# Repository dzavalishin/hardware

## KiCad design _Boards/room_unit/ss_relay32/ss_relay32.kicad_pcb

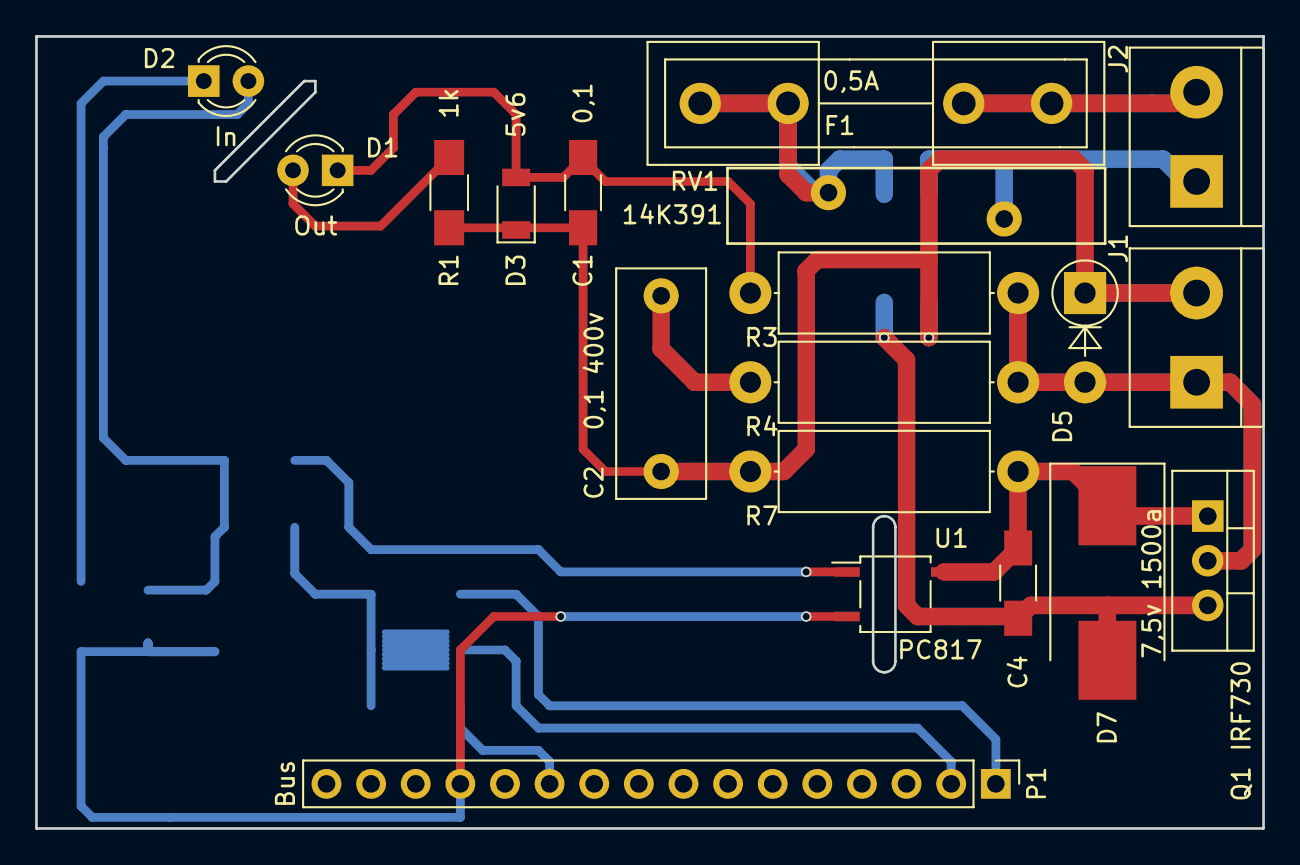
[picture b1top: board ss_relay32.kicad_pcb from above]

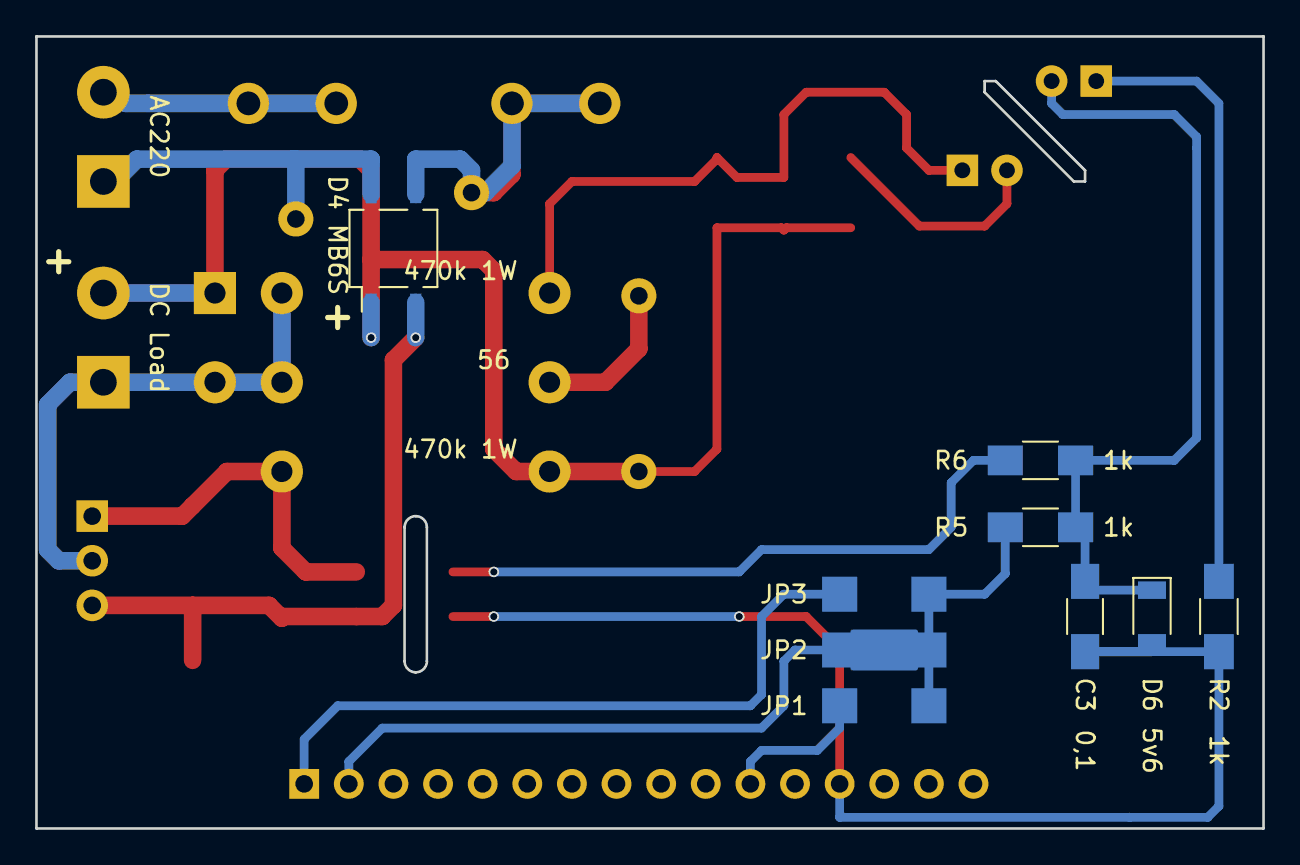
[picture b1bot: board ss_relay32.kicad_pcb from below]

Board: 2 copper layers, 69.8 x 45.1 mm, 28 parts (9 on the bottom side), 18 nets.

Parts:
C1, C3, C4: 0,1; C_1206_HandSoldering
C2: 0,1 400v; C_Rect_L13.0mm_W5.0mm_P10.00mm_FKS3_FKP3_MKS4
D1: Out; LED_D3.0mm
D2: In; LED_D3.0mm
D3, D6: 5v6; D_1206
D4: MB6S; Diode_Bridge_TO-269AA
D5: RL206; D_DO-15_P5.08mm_Vertical_AnodeUp
D7: 7,5v 1500a; D_SMC_Handsoldering
F1: 0,5A; Fuseholder5x20_horiz_open_inline_Type-I
J1: DC Load; TerminalBlock_bornier-2_P5.08mm
J2: AC220; TerminalBlock_bornier-2_P5.08mm
JP1, JP3: Jumper; NetTie-I_SMD
JP2: Jumper; NetTie-I_Connected_SMD
P1: Bus; Pin_Header_Straight_1x16_Pitch2.54mm
Q1: IRF730; TO-220-3_Vertical
R1, R2, R5, R6: 1k; R_1206_HandSoldering
R3, R7: 470k 1W; R_Axial_DIN0414_L11.9mm_D4.5mm_P15.24mm_Horizontal
R4: 56; R_Axial_DIN0414_L11.9mm_D4.5mm_P15.24mm_Horizontal
RV1: 14K391; RV_Disc_D21.5_W4.3_P10
U1: PC817; SOP-4_3.8x4.1mm_Pitch2.54mm

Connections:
/+220: C1.1, C2.1, D3.1, D4.1, D5.1, J1.2, R1.1, R7.1
/DO0: JP2.1, P1.2
/DO1: JP3.1, P1.1
/DO2: JP1.1, P1.11
/Gate: C4.1, D7.1, Q1.1, R7.2, U1.4
/IN: JP1.2, JP2.2, JP3.2, R5.2
/Load: D5.2, J1.1, Q1.2, R3.2, R4.2
/OGND: C4.2, D4.2, D7.2, Q1.3, U1.3
GND: C3.2, D6.2, P1.13, R2.2, U1.2
unnamed: C1.2, D1.1, D3.2, R3.1
unnamed: C2.2, R4.1
unnamed: C3.1, D2.2, D6.1, R5.1, R6.2
unnamed: D1.2, R1.2
unnamed: D2.1, R2.1
unnamed: D4.3, F1.2, RV1.1
unnamed: D4.4, J2.1, RV1.2
unnamed: F1.1, J2.2
unnamed: R6.1, U1.1

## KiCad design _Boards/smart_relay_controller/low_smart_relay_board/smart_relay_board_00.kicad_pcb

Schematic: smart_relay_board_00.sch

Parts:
C1, C32, C33: 0,1; C_1206_HandSoldering
C34: 47,0; CP_Elec_6.3x7.7
D23: 1n4148; D_MiniMELF_Handsoldering
J1: Di0-2; TerminalBlock_bornier-4_P5.08mm
J2: Di3-5; TerminalBlock_bornier-4_P5.08mm
J3: Di_6; TerminalBlock_bornier-2_P5.08mm
J4: Di_7; TerminalBlock_bornier-2_P5.08mm
J13: CPU; Pin_Header_Straight_2x06_Pitch2.54mm
J14: Power; TerminalBlock_bornier-2_P5.08mm
J15: RS485; TerminalBlock_bornier-2_P5.08mm
J16: Term485; Pin_Header_Straight_1x02_Pitch2.54mm
Q1: Q_NMOS_DGS; TO-92_Molded_Narrow_Oval
R4, R25: 1k; R_1206_HandSoldering
R20: 47; R_1206_HandSoldering
R24: 47k; R_1206_HandSoldering
U3: TPIC6595; DIP-20_W7.62mm_Socket_LongPads
U4: 74LS166; DIP-16_W7.62mm_Socket_LongPads

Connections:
+5V: C32.1, C33.1, C34.1, J13.7, R4.1, R24.1, U3.2, U4.16 (VCC); also elsewhere on the board
/MISO: D23.2, J13.2
/MOSI: J13.1, U3.3
/SCK: J13.5, U3.13, U4.7 (Clk)
/SS1: J13.4, Q1.3, U4.15 (PE)
/Sheet_relay_pair_0/Relay_In_Minus: J1.2; also elsewhere on the board
/Sheet_relay_pair_0/Relay_In_Plus: J1.1; also elsewhere on the board
/Sheet_relay_pair_1/Relay_In_Minus: J1.3; also elsewhere on the board
/Sheet_relay_pair_2/Relay_In_Minus: J1.4; also elsewhere on the board
/Sheet_relay_pair_4/Relay_In_Minus: J2.3; also elsewhere on the board
/Sheet_relay_pair_5/Relay_In_Minus: J2.4; also elsewhere on the board
/Simple_Di_Do_6/DI_B: J3.2; also elsewhere on the board
/Simple_Di_Do_6/Di_A: J3.1; also elsewhere on the board
/Simple_Di_Do_7/DI_B: J4.2; also elsewhere on the board
/Simple_Di_Do_7/Di_A: J4.1; also elsewhere on the board
/~CLR: C1.1, R4.2, U3.8, U4.9 (Clr)
/~SS0: J13.3, U3.12
CPU_Di0: U4.2 (A); also elsewhere on the board
CPU_Di1: U4.3 (B); also elsewhere on the board
CPU_Di2: U4.4 (C); also elsewhere on the board
CPU_Di3: U4.5 (D); also elsewhere on the board
CPU_Di4: U4.10 (E); also elsewhere on the board
CPU_Di5: U4.11 (F); also elsewhere on the board
CPU_Di6: U4.12 (G); also elsewhere on the board
CPU_Di7: U4.14 (H); also elsewhere on the board
CPU_Do0: U3.4; also elsewhere on the board
CPU_Do1: U3.5; also elsewhere on the board
CPU_Do2: U3.6; also elsewhere on the board
CPU_Do3: U3.7, U3.14; also elsewhere on the board
CPU_Do5: U3.15; also elsewhere on the board
CPU_Do6: U3.16; also elsewhere on the board
CPU_Do7: U3.17; also elsewhere on the board
GND: C1.2, C32.2, C33.2, C34.2, J13.6, J13.8, U3.1, U3.9, U3.10, U3.11, U3.19, U3.20, U4.1 (Ds), U4.6 (CE), U4.8 (GND); also elsewhere on the board
unnamed: D23.1, Q1.1, R24.2
unnamed: J13.9, J14.1
unnamed: J13.10, J15.2, R20.2
unnamed: J13.11, J14.2
unnamed: J13.12, J15.1, J16.1
unnamed: J16.2, R20.1
unnamed: Q1.2, R25.2
unnamed: R25.1, U4.13 (Qh)

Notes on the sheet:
Poor man's 3 state out

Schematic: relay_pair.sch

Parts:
C2, C4, C7: 0,1; C_1206_HandSoldering
C3: 0,022 x 400v; C_Rect_L13.0mm_W5.0mm_P10.00mm_FKS3_FKP3_MKS4
D1: 5v6; D_MiniMELF_Handsoldering
D3: 1n4148; D_MiniMELF_Handsoldering
D5: MB6S; SO-4_4.4x3.6mm_Pitch2.54mm
J5: Do_Adv; TerminalBlock_bornier-3_P5.08mm
R1, R2, R5: 1k; R_1206_HandSoldering
R3: 100 1w; R_Axial_DIN0309_L9.0mm_D3.2mm_P12.70mm_Horizontal
RL11, RL12: HK4100F; Relay_SPDT_HK4100F
U5: LTV-817; SO-4_7.6x3.6mm_Pitch2.54mm

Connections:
+5V: D3.1, R5.1, RL12.5; also elsewhere on the board
/Sheet_relay_pair_0/Relay_In_Plus: D5.3; also elsewhere on the board
/Sheet_relay_pair_1/Relay_In_Minus: D5.4; also elsewhere on the board
CPU_Di0: C7.1, R5.2, U5.4; also elsewhere on the board
CPU_Do0: D3.2; also elsewhere on the board
CPU_Do3: RL12.2; also elsewhere on the board
GND: C7.2, U5.3; also elsewhere on the board
unnamed 33: C2.1, C4.2, D1.2, U5.2; also elsewhere on the board
unnamed 34: C2.2, D1.1, R1.2, R2.1; also elsewhere on the board
unnamed 35: C3.1, J5.3; also elsewhere on the board
unnamed: C3.2, R3.1
unnamed: C4.1, R2.2, U5.1
unnamed 45: D5.2 (-); also elsewhere on the board
unnamed 56: RL11.5; also elsewhere on the board
unnamed 57: RL11.2; also elsewhere on the board
unnamed 58: RL11.1, RL11.6; also elsewhere on the board
unnamed 71: R1.1; also elsewhere on the board
unnamed 72: D5.1 (+); also elsewhere on the board
unnamed 80: J5.1, R3.2; also elsewhere on the board
unnamed 81: J5.2; also elsewhere on the board
unnamed 90: RL12.1, RL12.6; also elsewhere on the board
unnamed 91: RL11.3, RL12.4; also elsewhere on the board
unnamed: RL11.4, RL12.3

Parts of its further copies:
C5, C8, C10, C11, C13, C14, C16, C17, C25, C26, C27, C28, C29, C30, C31: 0,1; C_1206_HandSoldering
C6, C9, C12, C15, C18: 0,022 x 400v; C_Rect_L13.0mm_W5.0mm_P10.00mm_FKS3_FKP3_MKS4
D2, D8, D11, D14, D17: MB6S; SO-4_4.4x3.6mm_Pitch2.54mm
D4, D7, D10, D13, D16: 5v6; D_MiniMELF_Handsoldering
D6, D9, D12, D15, D18: 1n4148; D_MiniMELF_Handsoldering
J6, J7, J8, J9, J10: Do_Adv; TerminalBlock_bornier-3_P5.08mm
R6, R7, R9, R10, R11, R12, R14, R15, R16, R17, R19, R21, R22, R26, R27: 1k; R_1206_HandSoldering
R8, R13, R18, R23, R28: 100 1w; R_Axial_DIN0309_L9.0mm_D3.2mm_P12.70mm_Horizontal
RL1, RL2, RL3, RL4, RL5, RL6, RL7, RL8, RL9, RL10: HK4100F; Relay_SPDT_HK4100F
U6, U7, U8, U9, U10: LTV-817; SO-4_7.6x3.6mm_Pitch2.54mm

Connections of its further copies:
+5V: D6.1, D9.1, D12.1, D15.1, D18.1, R9.1, R10.1, R14.1, R15.1, R19.1, RL2.5, RL4.5, RL6.5, RL8.5, RL10.5; also elsewhere on the board
/Sheet_relay_pair_0/Relay_In_Minus: D2.4; also elsewhere on the board
/Sheet_relay_pair_0/Relay_In_Plus: D2.3, D8.3; also elsewhere on the board
/Sheet_relay_pair_2/Relay_In_Minus: D8.4; also elsewhere on the board
/Sheet_relay_pair_4/Relay_In_Minus: D17.4; also elsewhere on the board
/Sheet_relay_pair_5/Relay_In_Minus: D11.4; also elsewhere on the board
CPU_Di1: C13.1, R9.2, U6.4; also elsewhere on the board
CPU_Di2: C25.1, R10.2, U7.4; also elsewhere on the board
CPU_Di3: C29.1, R15.2, U9.4; also elsewhere on the board
CPU_Di4: C31.1, R19.2, U10.4; also elsewhere on the board
CPU_Di5: C27.1, R14.2, U8.4; also elsewhere on the board
CPU_Do0: RL2.2; also elsewhere on the board
CPU_Do1: D6.2, RL4.2; also elsewhere on the board
CPU_Do2: D9.2, RL6.2; also elsewhere on the board
CPU_Do3: D15.2, D18.2, RL10.2; also elsewhere on the board
CPU_Do5: D12.2, RL8.2; also elsewhere on the board
GND: C13.2, C25.2, C27.2, C29.2, C31.2, U6.3, U7.3, U8.3, U9.3, U10.3; also elsewhere on the board
unnamed 33: D2.2 (-), RL1.5; also elsewhere on the board
unnamed 34: RL1.2; also elsewhere on the board
unnamed 35: RL1.1, RL1.6; also elsewhere on the board
unnamed: C5.2, D4.1, R6.2, R7.1, RL3.2
unnamed: C6.1, J6.3, RL3.1, RL3.6
unnamed: C6.2, R8.1
unnamed: C8.2, D7.1, R11.2, R12.1, RL5.2
unnamed: C9.1, J7.3, RL5.1, RL5.6
unnamed: C9.2, R13.1
unnamed: C10.1, R7.2, U6.1
unnamed 45: C5.1, C10.2, D4.2, RL3.5, U6.2; also elsewhere on the board
unnamed: C11.1, C26.2, D10.2, D11.2 (-), RL7.5, U8.2
unnamed: C11.2, D10.1, R16.2, R17.1, RL7.2
unnamed: C12.1, J8.3, RL7.1, RL7.6
unnamed: C12.2, R18.1
unnamed: C14.1, C28.2, D13.2, D14.2 (-), RL9.5, U9.2
unnamed: C14.2, D13.1, R21.2, R22.1, RL9.2
unnamed: C15.1, J9.3, RL9.1, RL9.6
unnamed: C15.2, R23.1
unnamed: C16.1, R12.2, U7.1
unnamed: C8.1, C16.2, D7.2, D8.2 (-), RL5.5, U7.2
unnamed 56: C17.1, C30.2, D16.2, D17.2 (-), U10.2; also elsewhere on the board
unnamed 57: C17.2, D16.1, R26.2, R27.1; also elsewhere on the board
unnamed 58: C18.1, J10.3; also elsewhere on the board
unnamed: C18.2, R28.1
unnamed: C26.1, R17.2, U8.1
unnamed: C28.1, R22.2, U9.1
unnamed: C30.1, R27.2, U10.1
unnamed 71: D2.1 (+); also elsewhere on the board
unnamed 72: R6.1; also elsewhere on the board
unnamed: D8.1 (+), R11.1
unnamed: D11.1 (+), R16.1
unnamed: D14.1 (+), R21.1
unnamed: D17.1 (+), R26.1
unnamed 80: RL2.1, RL2.6; also elsewhere on the board
unnamed 81: RL1.3, RL2.4; also elsewhere on the board
unnamed: J6.1, R8.2, RL4.1, RL4.6
unnamed: J6.2, RL3.3, RL4.4
unnamed: J7.1, R13.2, RL6.1, RL6.6
unnamed: J7.2, RL5.3, RL6.4
unnamed: J8.1, R18.2, RL8.1, RL8.6
unnamed: J8.2, RL7.3, RL8.4
unnamed: J9.1, R23.2, RL10.1, RL10.6
unnamed: J9.2, RL9.3, RL10.4
unnamed 90: J10.1, R28.2; also elsewhere on the board
unnamed 91: J10.2; also elsewhere on the board
unnamed: RL1.4, RL2.3
unnamed: RL3.4, RL4.3
unnamed: RL5.4, RL6.3
unnamed: RL7.4, RL8.3
unnamed: RL9.4, RL10.3

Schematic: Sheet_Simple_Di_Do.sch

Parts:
C19, C21: 0,1; C_1206_HandSoldering
C20: 0,022 x 400v; C_Rect_L13.0mm_W5.0mm_P10.00mm_FKS3_FKP3_MKS4
D20: 1N4148; D_MiniMELF_Handsoldering
D21: MB6S; SO-4_4.4x3.6mm_Pitch2.54mm
J11: Do; TerminalBlock_bornier-3_P5.08mm
R31: 22k; R_1206_HandSoldering
R32: 100 1w; R_Axial_DIN0309_L9.0mm_D3.2mm_P12.70mm_Horizontal
R34: 1k; R_1206_HandSoldering
RL14: HK4100F; Relay_SPDT_HK4100F
U1: LTV-817; SO-4_7.6x3.6mm_Pitch2.54mm

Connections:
+5V: D20.1, R34.1, RL14.5; also elsewhere on the board
/Simple_Di_Do_6/Di_A: R31.2; also elsewhere on the board
/Simple_Di_Do_7/DI_B: D21.4; also elsewhere on the board
CPU_Di6: C21.1, R34.2, U1.4; also elsewhere on the board
CPU_Do6: D20.2; also elsewhere on the board
CPU_Do7: RL14.2; also elsewhere on the board
GND: C21.2, U1.3; also elsewhere on the board
unnamed 60: C19.1, U1.1; also elsewhere on the board
unnamed 61: C19.2, U1.2; also elsewhere on the board
unnamed: C20.1, R32.2
unnamed 63: C20.2, J11.2; also elsewhere on the board
unnamed 64: D21.1 (+); also elsewhere on the board
unnamed 65: D21.2 (-); also elsewhere on the board
unnamed 67: RL14.1, RL14.6; also elsewhere on the board
unnamed 77: R31.1; also elsewhere on the board
unnamed 78: D21.3; also elsewhere on the board
unnamed 92: J11.1; also elsewhere on the board
unnamed 93: J11.3, R32.1; also elsewhere on the board
unnamed 94: RL14.3; also elsewhere on the board
unnamed 95: RL14.4; also elsewhere on the board

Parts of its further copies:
C22, C24: 0,1; C_1206_HandSoldering
C23: 0,022 x 400v; C_Rect_L13.0mm_W5.0mm_P10.00mm_FKS3_FKP3_MKS4
D19: MB6S; SO-4_4.4x3.6mm_Pitch2.54mm
D22: 1N4148; D_MiniMELF_Handsoldering
J12: Do; TerminalBlock_bornier-3_P5.08mm
R36: 22k; R_1206_HandSoldering
R37: 100 1w; R_Axial_DIN0309_L9.0mm_D3.2mm_P12.70mm_Horizontal
R39: 1k; R_1206_HandSoldering
RL13: HK4100F; Relay_SPDT_HK4100F
U2: LTV-817; SO-4_7.6x3.6mm_Pitch2.54mm

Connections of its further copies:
+5V: D22.1, R39.1, RL13.5; also elsewhere on the board
/Simple_Di_Do_6/DI_B: D19.4; also elsewhere on the board
/Simple_Di_Do_7/Di_A: R36.2; also elsewhere on the board
CPU_Di7: C24.1, R39.2, U2.4; also elsewhere on the board
CPU_Do6: RL13.2; also elsewhere on the board
CPU_Do7: D22.2; also elsewhere on the board
GND: C24.2, U2.3; also elsewhere on the board
unnamed 60: D19.1 (+); also elsewhere on the board
unnamed 61: D19.2 (-); also elsewhere on the board
unnamed 63: RL13.1, RL13.6; also elsewhere on the board
unnamed 64: C22.1, U2.1; also elsewhere on the board
unnamed 65: C22.2, U2.2; also elsewhere on the board
unnamed: C23.1, R37.2
unnamed 67: C23.2, J12.2; also elsewhere on the board
unnamed 77: D19.3; also elsewhere on the board
unnamed 78: R36.1; also elsewhere on the board
unnamed 92: RL13.3; also elsewhere on the board
unnamed 93: RL13.4; also elsewhere on the board
unnamed 94: J12.1; also elsewhere on the board
unnamed 95: J12.3, R37.1; also elsewhere on the board

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
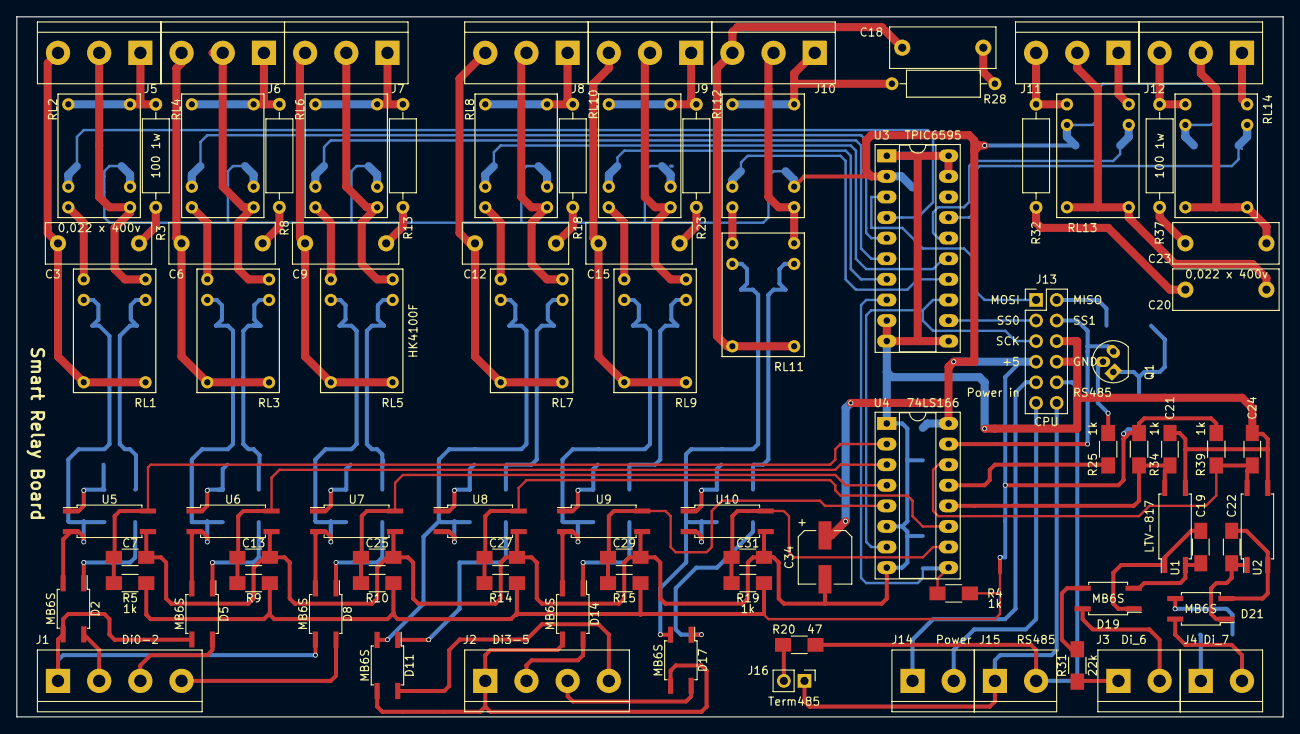
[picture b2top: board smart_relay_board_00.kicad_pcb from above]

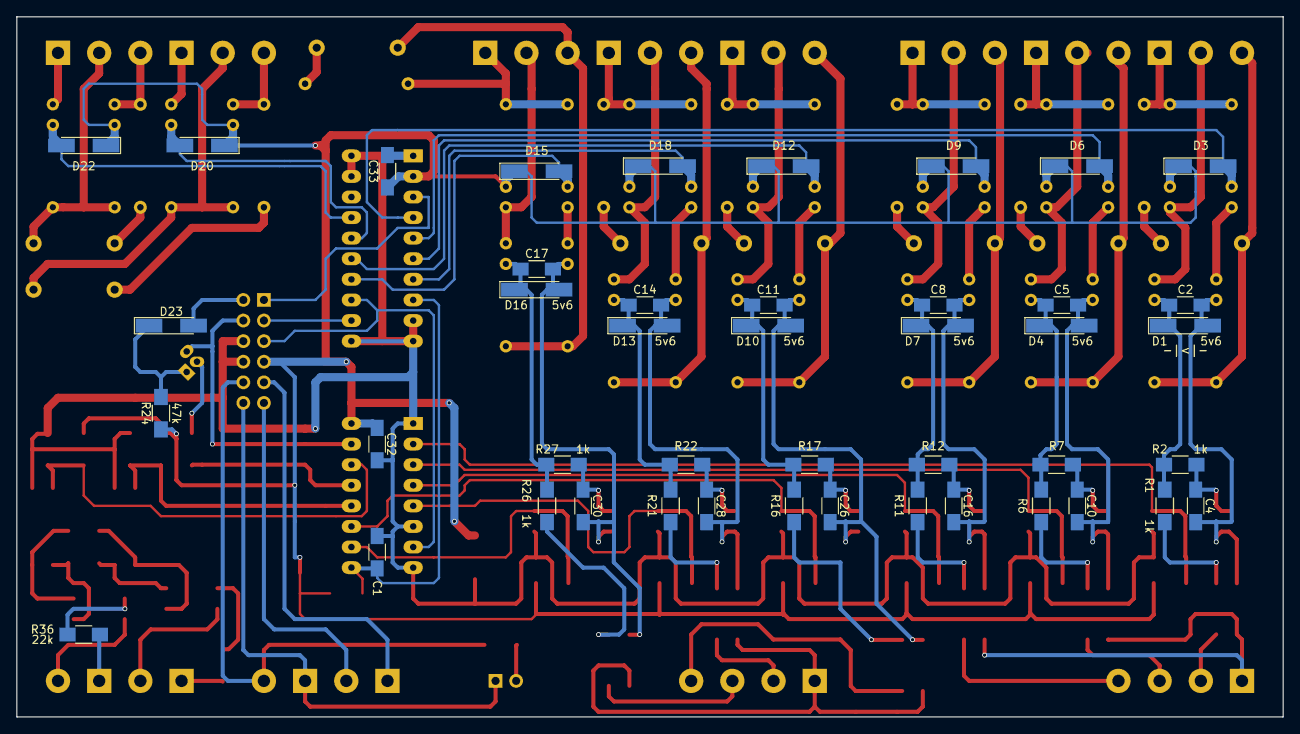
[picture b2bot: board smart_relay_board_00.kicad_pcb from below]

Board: 2 copper layers, 156.2 x 86.4 mm, 132 parts (44 on the bottom side), 111 nets.

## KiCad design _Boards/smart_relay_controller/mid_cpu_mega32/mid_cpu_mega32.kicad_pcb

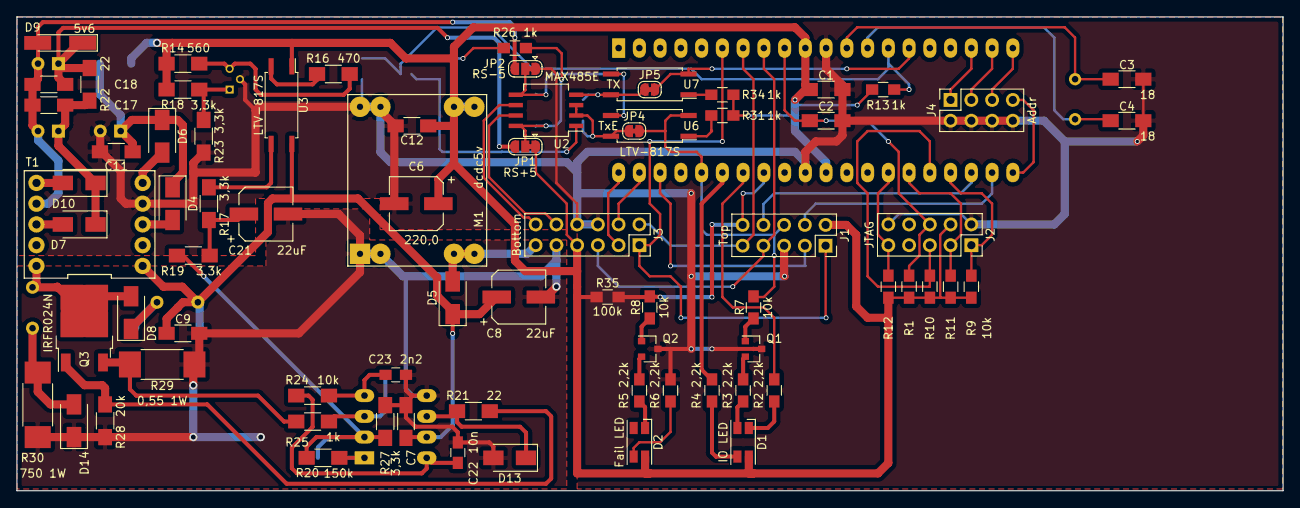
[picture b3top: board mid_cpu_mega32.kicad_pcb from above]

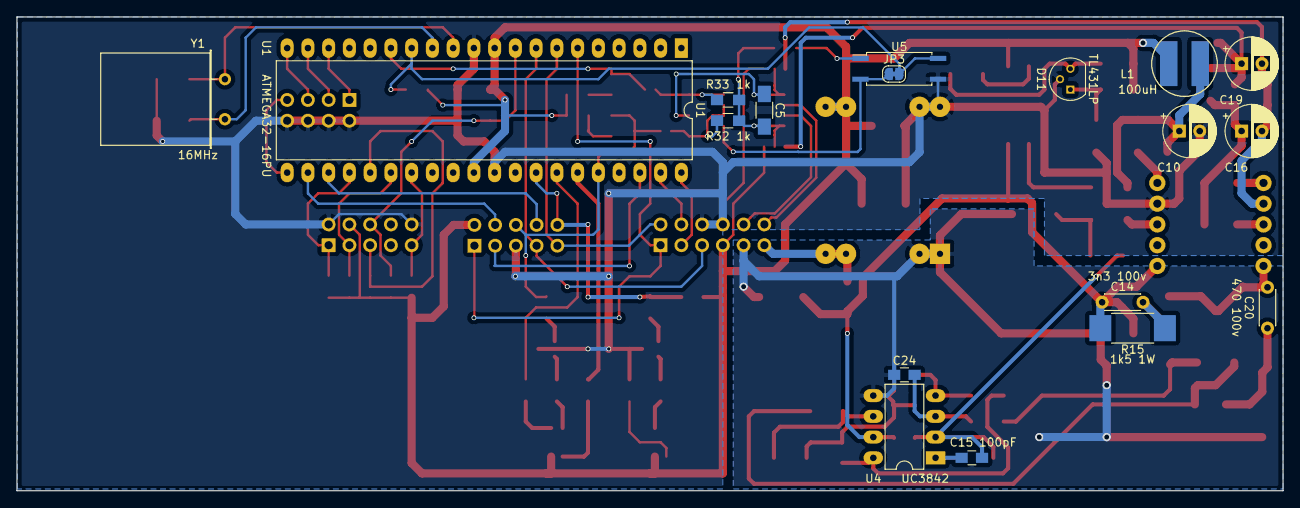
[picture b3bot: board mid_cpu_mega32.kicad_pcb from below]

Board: 2 copper layers, 155.0 x 58.0 mm, 93 parts (18 on the bottom side), 73 nets.

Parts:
C1, C2, C5, C7, C9, C11, C12, C17, C18: 0,1; C_1206_HandSoldering
C3, C4: 18; C_1206_HandSoldering
C6: 220,0; CP_Elec_6.3x5.8
C8, C21: 22uF; CP_Elec_6.3x4.5
C10, C16, C19: 470uF; CP_Radial_D6.3mm_P2.50mm
C14: 3n3 100v; C_Disc_D4.3mm_W1.9mm_P5.00mm
C15: 100pF; C_0805_HandSoldering
C20: 470 100v; C_Disc_D4.3mm_W1.9mm_P5.00mm
C22: 10n; C_0805_HandSoldering
C23: 2n2; C_0805_HandSoldering
C24: 470; C_0805_HandSoldering
D1: IO LED; LED_RGB_1210
D2: Fail LED; LED_RGB_1210
D4, D5, D6, D7, D8, D10, D13, D14: 1N5822; D_SMA
D9: 5v6; D_MiniMELF_Handsoldering
D11: TL431LP; TO-92_Molded_Narrow
J1: Top; Socket_Strip_Straight_2x05_Pitch2.54mm
J2: JTAG; Socket_Strip_Straight_2x05_Pitch2.54mm
J3: Bottom; Socket_Strip_Straight_2x06_Pitch2.54mm
J4: Addr; Socket_Strip_Straight_2x04_Pitch2.54mm
JP1: RS+5; SolderJumper-3_P1.3mm_Bridged12_RoundedPad1.0x1.5mm
JP2: RS-5; SolderJumper-3_P1.3mm_Bridged12_RoundedPad1.0x1.5mm
JP3: RX; SolderJumper-2_P1.3mm_Bridged_RoundedPad1.0x1.5mm
JP4: TxE; SolderJumper-2_P1.3mm_Bridged_RoundedPad1.0x1.5mm
JP5: TX; SolderJumper-2_P1.3mm_Bridged_RoundedPad1.0x1.5mm
L1: 100uH; cd54
M1: dcdc5v
Q1, Q2: PZT2222A; SOT-23
Q3: IRFR024N; TO-252-2
R1, R7, R8, R9, R10, R11, R12: 10k; R_0805_HandSoldering
R2, R3, R4, R5, R6: 2,2k; R_0805_HandSoldering
R13, R26, R31, R32, R33, R34: 1k; R_0805_HandSoldering
R14: 560; R_1206_HandSoldering
R15: 1k5 1W; R_2512_HandSoldering
R16: 470; R_1206_HandSoldering
R17, R18, R19, R23, R27: 3,3k; R_1206_HandSoldering
R20: 150k; R_1206_HandSoldering
R21, R22: 22; R_1206_HandSoldering
R24: 10k; R_1206_HandSoldering
R25: 1k; R_1206_HandSoldering
R28: 20k; R_1206_HandSoldering
R29: 0,55 1W; R_2512_HandSoldering
R30: 750 1W; R_2512_HandSoldering
R35: 100k; R_0805_HandSoldering
T1: EE16_24_05_Transformer; EE16_Transformer
U1: ATMEGA32-16PU; DIP-40_W15.24mm_LongPads
U2: MAX485E; SO-8_5.3x6.2mm_Pitch1.27mm
U3, U5, U6, U7: LTV-817S; SO-4_7.6x3.6mm_Pitch2.54mm
U4: UC3842; DIP-8_W7.62mm_LongPads
Y1: 16MHz; Crystal_HC49-U_Horizontal

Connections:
/DCDC/+24: C7.1, C8.1, C9.1, C14.2, D5.1, R15.2, T1.1, U3.4, U4.7
/Debug_Led_0: R4.2, U1.35
/Debug_Led_1: R2.2, U1.34
/Fail_Led: J1.10, R8.2, R35.2, U1.33
/IO_Led: Q1.2, R3.2
/MISO: J1.9, J3.2, U1.7
/MOSI: J1.1, J3.1, U1.6
/Pwr24A: C7.2, C8.2, C9.2, C21.2, C22.1, C23.1, C24.1, D13.2, D14.1, J3.9, M1.1, R27.1, R28.1, R29.1, R30.1, U4.5
/Pwr24B: D5.2, J3.11, M1.2
/RS485A: J3.12, U2.6
/RS485B: J3.10, U2.7
/RS+5: C18.1, C19.1, D9.1, JP1.3, R22.1
/RS-5: C16.2, C17.2, C18.2, C19.2, D9.2, JP2.3, T1.7
/Reset: C2.1, J2.6, R1.2, U1.9
/Rx: JP3.2, R13.1, U1.14, U5.4
/SCK: J1.7, J3.5, U1.8
/SCL: J1.4, U1.22
/SDA: J1.8, U1.23
/SS0: J3.3, U1.40
/SS1: J3.4, U1.39
/SS2: J1.3, U1.38
/TCK: J2.1, R9.2, U1.24
/TDI: J2.9, R12.2, U1.27
/TDO: J2.3, R11.2, U1.26
/TMS: J2.5, R10.2, U1.25
/Tx: JP5.2, U1.15, U7.2
/TxE: J1.6, JP4.2, R7.2, U1.36, U6.2
GND: C1.2, C2.2, C3.2, C4.2, C6.2, C10.2, C11.2, C12.2, D11.2, J1.5, J2.2, J2.10, J3.6, J3.8, J4.2, J4.4, J4.6, J4.8, JP2.1, M1.4, Q1.3, Q2.3, R6.2, R23.1, T1.4, U1.11, U1.31, U5.3
unnamed: C3.1, U1.12, Y1.1
unnamed: C4.1, U1.13, Y1.2
unnamed: C5.1, JP1.2, R26.1, R32.2, R33.2, U2.8
unnamed: C5.2, JP2.2, U2.5, U6.3, U7.3
unnamed: C10.1, C11.1, D4.1, D6.1, L1.2
unnamed: C14.1, D8.1, R15.1
unnamed: C15.1, R20.1, U4.1
unnamed: C15.2, R19.1, R20.2, R27.2, U4.2
unnamed: C16.1, C17.1, D7.1, D10.1, R22.2
unnamed: C20.1, D14.2, R30.2
unnamed: C20.2, D8.2, Q3.2, T1.10
unnamed: C21.1, R17.1, R19.2
unnamed: C22.2, R24.2, U4.8
unnamed: C23.2, R24.1, U4.4
unnamed: C24.2, R25.2, U4.3
unnamed: D1.1, R2.1
unnamed: D1.2, R3.1
unnamed: D1.3, R4.1
unnamed: D2.1, R5.1
unnamed: D2.3, R6.1
unnamed: D4.2, T1.3
unnamed: D6.2, T1.5
unnamed: D7.2, T1.8
unnamed: D10.2, T1.6
unnamed: D11.1, R18.1, R23.2
unnamed: D11.3, R14.1, R16.1
unnamed: D13.1, R21.2, U4.6
unnamed: J4.1, U1.18
unnamed: J4.3, U1.19
unnamed: J4.5, U1.20
unnamed: J4.7, U1.21
unnamed: JP3.1, U2.1, U5.2
unnamed: JP4.1, R32.1, U2.2, U2.3, U6.4
unnamed: JP5.1, R33.1, U2.4, U7.4
unnamed: Q1.1, R7.1
unnamed: Q2.1, R8.1
unnamed: Q2.2, R5.2
unnamed: Q3.1, R21.1, R28.2
unnamed: Q3.3, R25.1, R29.2
unnamed: R16.2, U3.2
unnamed: R17.2, U3.3
unnamed: R26.2, U5.1
unnamed: R31.1, U6.1
unnamed: R34.1, U7.1
VCC: C1.1, C6.1, C12.1, D1.4, D2.4, J1.2, J2.4, J3.7, JP1.1, L1.1, M1.3, R1.1, R9.1, R10.1, R11.1, R12.1, R13.2, R14.2, R18.2, R31.2, R34.2, R35.1, U1.10, U1.30, U3.1

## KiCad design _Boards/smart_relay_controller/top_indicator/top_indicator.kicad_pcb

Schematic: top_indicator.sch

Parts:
C1: 1,0; C_0805_HandSoldering
C2, C3, C4, C5, C6: 0,1; C_1206_HandSoldering
C7, C8, C9: 10.0; C_1206_HandSoldering
D1, D9: L0; LED_1206_HandSoldering
D2, D10: L1; LED_1206_HandSoldering
D3, D11: L2; LED_1206_HandSoldering
D4, D12: L3; LED_1206_HandSoldering
D5, D13: L4; LED_1206_HandSoldering
D6, D14: L5; LED_1206_HandSoldering
D7, D15: L6; LED_1206_HandSoldering
D8, D16: L7; LED_1206_HandSoldering
D17: Io; LED_1206_HandSoldering
D18: Fail; LED_1206_HandSoldering
D19, D20, D21: DZ_LED_ARGB; LED_RGB_1210
J1: Bus; Socket_Strip_Straight_2x05_Pitch2.54mm
R1, R2, R3, R4, R5, R6, R7, R8, R9, R10, R11, R12, R13, R14, R15, R16, R17, R18, R19, R20, R21, R22, R23, R24, R25, R26, R27, R28, R29, R30, R31, R32, R33, R34: 1k; R_0805_HandSoldering
R35: 100k; R_0805_HandSoldering
SW1, SW2, SW3, SW4, SW5, SW6: SW_Push; SW_PUSH_6mm_h13mm
U1, U2, U3, U4: 74HC595; SOP-16_4.4x10.4mm_Pitch1.27mm

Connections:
/MISO: J1.9, R35.1, SW1.2, SW2.2, SW3.2, SW4.2, SW5.2, SW6.2
/MOSI: J1.1, U1.14 (SER)
/SCK: J1.7, U1.11 (SRCLK), U2.11 (SRCLK), U3.11 (SRCLK), U4.11 (SRCLK)
/SS: J1.3, U1.12 (RCLK), U2.12 (RCLK), U3.12 (RCLK), U4.12 (RCLK), U4.13 (G)
GND: C1.2, C2.2, C3.2, C4.2, C5.2, C6.2, C7.2, C8.2, C9.2, D1.1, D2.1, D3.1, D4.1, D5.1, D6.1, D7.1, D8.1, D9.1, D10.1, D11.1, D12.1, D13.1, D14.1, D15.1, D16.1, D17.1, D18.1, J1.5, R21.1, U1.8 (GND), U1.13 (G), U2.8 (GND), U2.13 (G), U3.8 (GND), U3.13 (G), U4.8 (GND)
unnamed: C1.1, R18.1, U1.10 (SRCLR), U2.10 (SRCLR), U3.10 (SRCLR), U4.10 (SRCLR)
unnamed: D1.2, R1.1
unnamed: D2.2, R2.1
unnamed: D3.2, R3.1
unnamed: D4.2, R4.1
unnamed: D5.2, R5.1
unnamed: D6.2, R6.1
unnamed: D7.2, R7.1
unnamed: D8.2, R8.1
unnamed: D9.2, R9.1
unnamed: D10.2, R10.1
unnamed: D11.2, R11.1
unnamed: D12.2, R12.1
unnamed: D13.2, R13.1
unnamed: D14.2, R14.1
unnamed: D15.2, R15.1
unnamed: D16.2, R16.1
unnamed: D17.2, R17.1
unnamed: D18.2, R19.1
unnamed: D19.1, R20.1
unnamed: D19.2, R22.1
unnamed: D19.3, R23.1
unnamed: D20.1, R24.1
unnamed: D20.2, R25.1
unnamed: D20.3, R26.1
unnamed: D21.1, R27.1
unnamed: D21.2, R28.1
unnamed: D21.3, R21.2
unnamed: J1.6, R17.2
unnamed: J1.10, R19.2
unnamed: R1.2, U1.15 (QA)
unnamed: R2.2, U1.1 (QB)
unnamed: R3.2, U1.2 (QC)
unnamed: R4.2, U1.3 (QD)
unnamed: R5.2, U1.4 (QE)
unnamed: R6.2, U1.5 (QF)
unnamed: R7.2, U1.6 (QG)
unnamed: R8.2, U1.7 (QH)
unnamed: R9.2, U2.15 (QA)
unnamed: R10.2, U2.1 (QB)
unnamed: R11.2, U2.2 (QC)
unnamed: R12.2, U2.3 (QD)
unnamed: R13.2, U2.4 (QE)
unnamed: R14.2, U2.5 (QF)
unnamed: R15.2, U2.6 (QG)
unnamed: R16.2, U2.7 (QH)
unnamed: R20.2, U3.15 (QA)
unnamed: R22.2, U3.1 (QB)
unnamed: R23.2, U3.2 (QC)
unnamed: R24.2, U3.3 (QD)
unnamed: R25.2, U3.4 (QE)
unnamed: R26.2, U3.5 (QF)
unnamed: R27.2, U3.6 (QG)
unnamed: R28.2, U3.7 (QH)
unnamed: R29.1, SW1.1
unnamed: R29.2, U4.15 (QA)
unnamed: R30.1, SW2.1
unnamed: R30.2, U4.1 (QB)
unnamed: R31.1, SW3.1
unnamed: R31.2, U4.2 (QC)
unnamed: R32.1, SW4.1
unnamed: R32.2, U4.3 (QD)
unnamed: R33.1, SW5.1
unnamed: R33.2, U4.4 (QE)
unnamed: R34.1, SW6.1
unnamed: R34.2, U4.5 (QF)
unnamed: R35.2, U4.7 (QH)
unnamed: U1.9 (~QH), U2.14 (SER)
unnamed: U2.9 (~QH), U3.14 (SER)
unnamed: U3.9 (~QH), U4.14 (SER)
VCC: C2.1, C3.1, C4.1, C5.1, C6.1, C7.1, C8.1, C9.1, D19.4, D20.4, D21.4, J1.2, R18.2, U1.16 (VCC), U2.16 (VCC), U3.16 (VCC), U4.16 (VCC)

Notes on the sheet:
Inputs
Outputs
Keys are enabled on SS low to be read with MOSI line one by one (scan with register out)

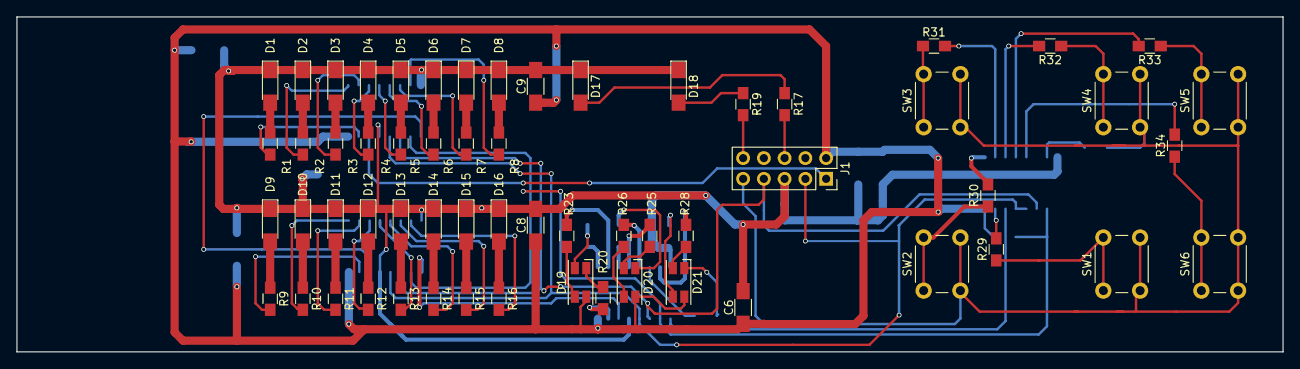
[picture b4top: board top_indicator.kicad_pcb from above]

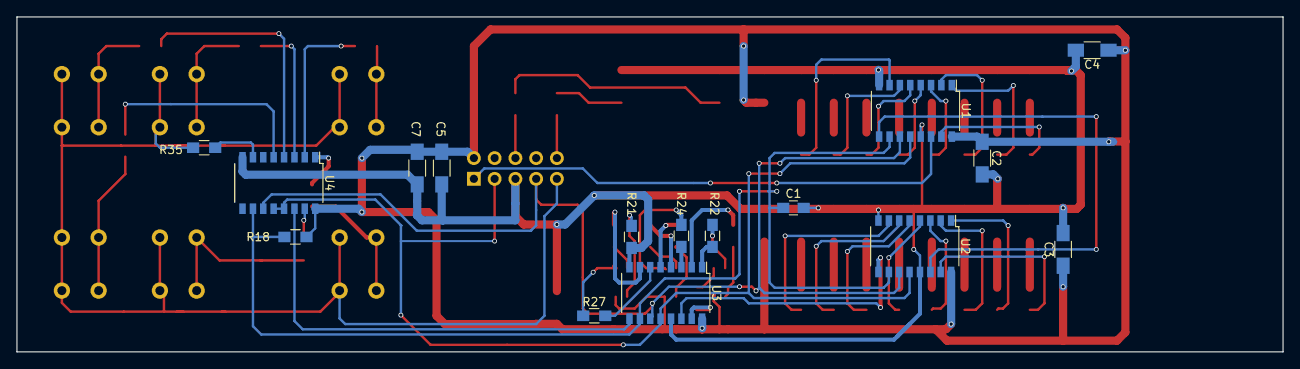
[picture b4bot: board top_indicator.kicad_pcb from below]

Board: 2 copper layers, 155.0 x 41.0 mm, 76 parts (16 on the bottom side), 76 nets.

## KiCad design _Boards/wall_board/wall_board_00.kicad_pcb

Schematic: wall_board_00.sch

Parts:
C1, C2, C3, C4: 0,1; C_1206_HandSoldering
C5, C6: 470,0; CP_Radial_D10.0mm_P2.50mm_P5.00mm
D1: Ch0; LED_1206_HandSoldering
D2: Ch1; LED_1206_HandSoldering
D3: Ch2; LED_1206_HandSoldering
D4: Ch3; LED_1206_HandSoldering
D5, D6: 4V7; D_MiniMELF_Handsoldering
D7: Di0; LED_1206_HandSoldering
D8: Di1; LED_1206_HandSoldering
D9: Do0; LED_1206_HandSoldering
D10: Do1; LED_1206_HandSoldering
D11, D12, D13: 1n4148; D_MiniMELF_Handsoldering
F1: Polyfuse; Fuse_SMD1206_HandSoldering
J1: Di; TerminalBlock_bornier-3_P5.08mm
J2: 1WireExt; TerminalBlock_bornier-3_P5.08mm
J3: +24; TerminalBlock_bornier-2_P5.08mm
J4: Do0; TerminalBlock_bornier-3_P5.08mm
J5: Do1; TerminalBlock_bornier-3_P5.08mm
J6: Conn_01x03_Male; Pin_Header_Straight_1x03_Pitch2.54mm
M1: dcdc5v
P1: Buttons 0-3; Pin_Header_Straight_1x05_Pitch2.54mm
P2, P3: CONN_01X20; Socket_Strip_Straight_1x20_Pitch2.54mm
P4: Enc; Pin_Header_Straight_1x04_Pitch2.54mm
P5: LCD2004; Socket_Strip_Straight_1x16_Pitch2.54mm
Q1, Q2, Q3: MMBT2222; SOT-23
R1, R2, R5, R6, R11, R12, R13, R14, R16: 1k; R_1206_HandSoldering
R3, R4: 560; R_1206_HandSoldering
R7, R8: 2,2k; R_1206_HandSoldering
R9, R10, R15: 470; R_1206_HandSoldering
R17: 4,7k; R_1206_HandSoldering
R18: 100; R_1206_HandSoldering
RL1, RL2: SRD-0XVDC-SL-C; Relay_SPDT_SANYOU_SRD_Series_Form_C
RV1: POT_TRIM; Potentiometer_Trimmer_Bourns_3339H_Horizontal
RV2, RV3: 36V; RV_Disc_D12_W3.9_P7.5
U1: DS2401; TO-92_Molded_Wide_Oval
U2: DS18B20; TO-92_Molded_Wide_Oval

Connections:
+5V: C4.2, C6.1, D1.2, D2.2, D3.2, D4.2, D7.2, D8.2, D9.2, D10.2, D11.1, D12.1, F1.1, M1.3, P2.19, P5.2, P5.15, R17.1, RL1.5, RL2.5, RV1.3, U2.3 (VDD)
/1Wire: P3.18, R17.2, R18.1, U1.2 (DQ), U2.2 (DQ)
/EncA: P3.1, P4.2
/EncB: P3.2, P4.3
/EncEnter: P3.4, P4.1
/LCDLED: J6.3, Q2.3
/PWM: P2.8, R15.1
Contrast: P5.3, RV1.2
Di0: C1.1, D5.1, P2.15, R3.1, R7.2
Di1: C2.1, D6.1, P2.16, R4.1, R8.2
Do0: P2.5, R9.1
Do1: P2.7, R10.1
unnamed: C3.2, F1.2, J2.1
unnamed: C5.1, D13.1, M1.2
unnamed: D1.1, R2.2
unnamed: D2.1, R6.2
unnamed: D3.1, R1.2
unnamed: D4.1, R5.2
unnamed: D7.1, R7.1
unnamed: D8.1, R8.1
unnamed: D9.1, R11.2
unnamed: D10.1, R12.2
unnamed: D11.2, Q1.3, R11.1, RL1.2
unnamed: D12.2, Q3.3, R12.1, RL2.2
unnamed: D13.2, J3.1
unnamed: J1.1, R3.2, RV2.1
unnamed: J1.3, R4.2, RV3.1
unnamed: J2.2, R18.2
unnamed: J4.1, RL1.4
unnamed: J4.2, RL1.1
unnamed: J4.3, RL1.3
unnamed: J5.1, RL2.4
unnamed: J5.2, RL2.1
unnamed: J5.3, RL2.3
unnamed: J6.2, P5.16
unnamed: P1.2, P2.12
unnamed: P1.3, P2.11
unnamed: P1.4, P2.10
unnamed: P1.5, P2.9
unnamed: P2.1, R5.1
unnamed: P2.2, R1.1
unnamed: P2.3, R6.1
unnamed: P2.4, R2.1
unnamed: P3.6, P5.4
unnamed: P3.7, P5.5
unnamed: P3.8, P5.6
unnamed: P3.10, P5.7
unnamed: P3.11, P5.8
unnamed: P3.12, P5.9
unnamed: P3.13, P5.10
unnamed: P3.14, P5.11
unnamed: P3.15, P5.12
unnamed: P3.16, P5.13
unnamed: P3.17, P5.14
unnamed: Q1.1, R9.2, R13.1
unnamed: Q2.1, R15.2, R16.1
unnamed: Q3.1, R10.2, R14.1

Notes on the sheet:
MMNet01 module

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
